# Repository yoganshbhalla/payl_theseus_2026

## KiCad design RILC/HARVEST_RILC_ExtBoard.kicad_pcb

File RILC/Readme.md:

Regolith Illumination for Light-based Characterisation
Extension Board for AS7331 and AS7343 Breakout Spectrometers, containing VIS, UV, NIR LEDs and control/driver circuitry.

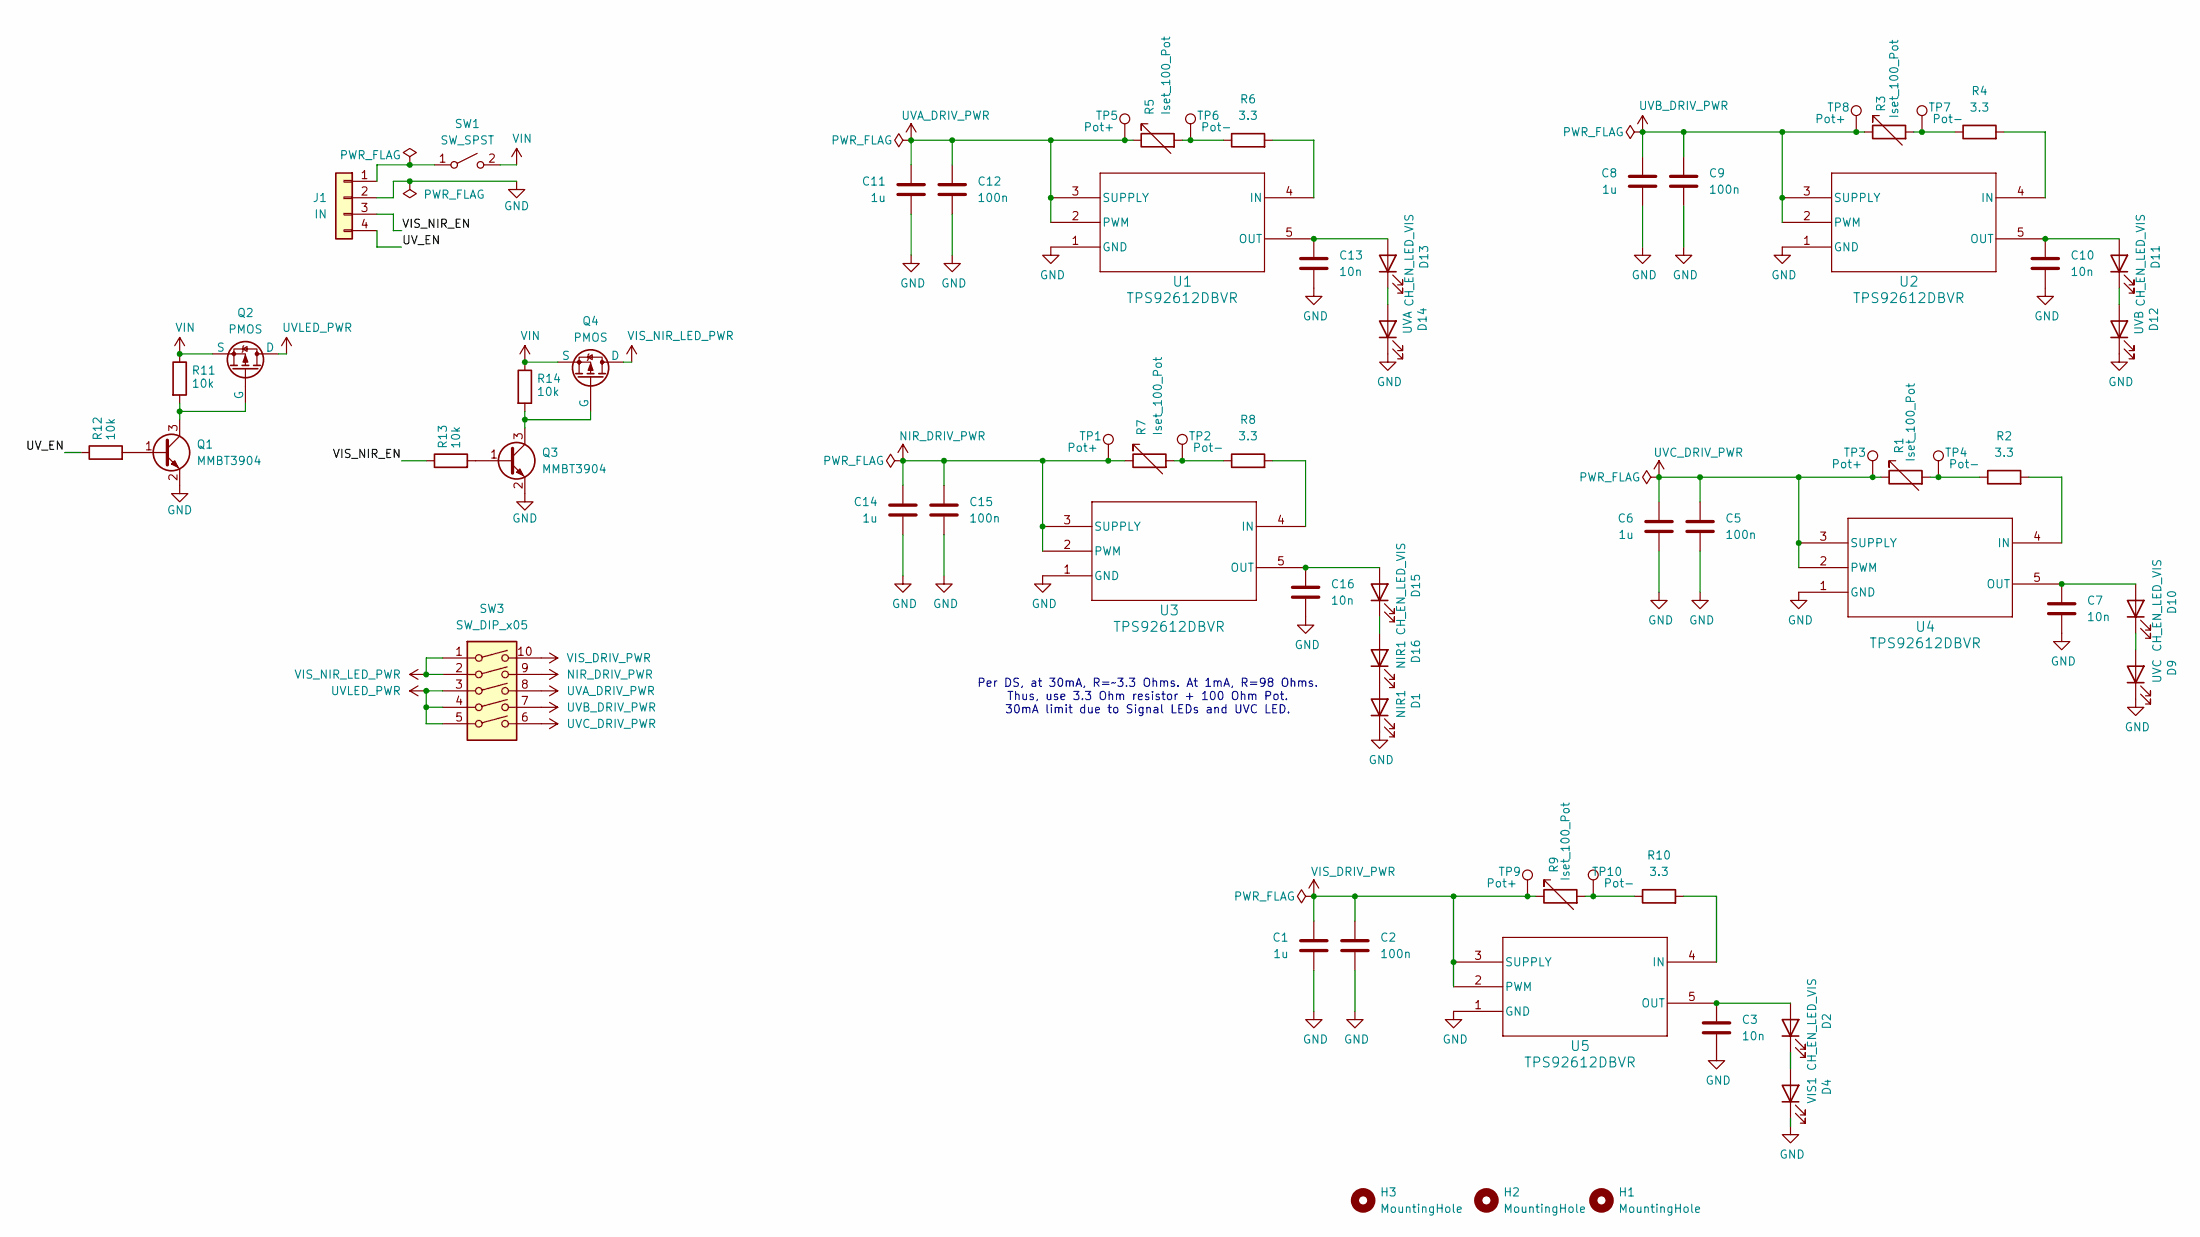
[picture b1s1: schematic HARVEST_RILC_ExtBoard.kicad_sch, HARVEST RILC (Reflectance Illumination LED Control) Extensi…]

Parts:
C1, C6, C8, C11, C14: 1u; C_0805_2012Metric_Pad1.18x1.45mm_HandSolder
C2, C5, C9, C12, C15: 100n; C_0805_2012Metric_Pad1.18x1.45mm_HandSolder
C3, C7, C10, C13, C16: 10n; C_0805_2012Metric_Pad1.18x1.45mm_HandSolder
D1, D16: NIR1; LED_0805_2012Metric_Pad1.15x1.40mm_HandSolder
D2, D10, D11, D13, D15: CH_EN_LED_VIS; LED_0805_2012Metric_Pad1.15x1.40mm_HandSolder
D4: VIS1; WL-SWTP_3014
D9: UVC; CR_0-275-120_VIS
D12: UVB; CHIP_1GF1A_SVI
D14: UVA; LED_0606
H1, H2, H3: MountingHole; MountingHole_2.2mm_M2
J1: IN; JST_XH_B4B-XH-A_1x04_P2.50mm_Vertical
Q1, Q3: MMBT3904; SOT-23
Q2, Q4: PMOS; SOT91P240X110-3N_DMG2305UX-7
R1, R3, R5, R7, R9: Iset_100_Pot; Potentiometer_Bourns_3296W_Vertical
R2, R4, R6, R8, R10: 3.3; R_0805_2012Metric_Pad1.20x1.40mm_HandSolder
R11, R12, R13, R14: 10k; R_0805_2012Metric_Pad1.20x1.40mm_HandSolder
SW1: SW_SPST; Switch_Toggle_SPDT_ANT11SF1CQE
SW3: SW_DIP_x05; SW_DIP_SPSTx05_Piano_CTS_Series194-5MSTN_W7.62mm_P2.54mm
TP1, TP3, TP5, TP8, TP9: Pot+; TestPoint_Pad_1.5x1.5mm
TP2, TP4, TP6, TP7, TP10: Pot-; TestPoint_Pad_1.5x1.5mm
U1, U2, U3, U4, U5: TPS92612DBVR; SOT_12DBVR_TEX

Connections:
/UV_EN: J1.4, R12.1
/VIS_NIR_EN: J1.3, R13.1
GND: C1.2, C2.2, C3.2, C5.2, C6.2, C7.2, C8.2, C9.2, C10.2, C11.2, C12.2, C13.2, C14.2, C15.2, C16.2, D1.1 (K), D4.1 (K), D9.1 (K), D12.1 (K), D14.1 (K), J1.2, Q1.2 (E), Q3.2 (E), U1.1 (GND), U2.1 (GND), U3.1 (GND), U4.1 (GND), U5.1 (GND)
NIR_DRIV_PWR: C14.1, C15.1, R7.1, SW3.9, TP1.1, U3.2 (PWM), U3.3 (SUPPLY)
unnamed: D1.2 (A), D16.1 (K)
unnamed: C3.1, D2.2 (A), U5.5 (OUT)
unnamed: D2.1 (K), D4.2 (A)
unnamed: C7.1, D10.2 (A), U4.5 (OUT)
unnamed: D9.2 (A), D10.1 (K)
unnamed: C10.1, D11.2 (A), U2.5 (OUT)
unnamed: D11.1 (K), D12.2 (A)
unnamed: C13.1, D13.2 (A), U1.5 (OUT)
unnamed: D13.1 (K), D14.2 (A)
unnamed: C16.1, D15.2 (A), U3.5 (OUT)
unnamed: D15.1 (K), D16.2 (A)
unnamed: J1.1, SW1.1 (A)
unnamed: Q1.1 (B), R12.2
unnamed: Q1.3 (C), Q2.2 (G), R11.2
unnamed: Q3.1 (B), R13.2
unnamed: Q3.3 (C), Q4.2 (G), R14.2
unnamed: R1.2, R2.1, TP4.1
unnamed: R3.2, R4.1, TP7.1
unnamed: R5.2, R6.1, TP6.1
unnamed: R7.2, R8.1, TP2.1
unnamed: R9.2, R10.1, TP10.1
unnamed: R6.2, U1.4 (IN)
unnamed: R4.2, U2.4 (IN)
unnamed: R8.2, U3.4 (IN)
unnamed: R2.2, U4.4 (IN)
unnamed: R10.2, U5.4 (IN)
UVA_DRIV_PWR: C11.1, C12.1, R5.1, SW3.8, TP5.1, U1.2 (PWM), U1.3 (SUPPLY)
UVB_DRIV_PWR: C8.1, C9.1, R3.1, SW3.7, TP8.1, U2.2 (PWM), U2.3 (SUPPLY)
UVC_DRIV_PWR: C5.1, C6.1, R1.1, SW3.6, TP3.1, U4.2 (PWM), U4.3 (SUPPLY)
UVLED_PWR: Q2.1 (D), SW3.3, SW3.4, SW3.5
VIN: Q2.3 (S), Q4.3 (S), R11.1, R14.1, SW1.2 (B)
VIS_DRIV_PWR: C1.1, C2.1, R9.1, SW3.10, TP9.1, U5.2 (PWM), U5.3 (SUPPLY)
VIS_NIR_LED_PWR: Q4.1 (D), SW3.1, SW3.2

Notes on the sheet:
Per DS, at 30mA, R=~3.3 Ohms. At 1mA, R=98 Ohms. Thus, use 3.3 Ohm resistor + 100 Ohm Pot. 30mA limit due to Signal LEDs and UVC LED.

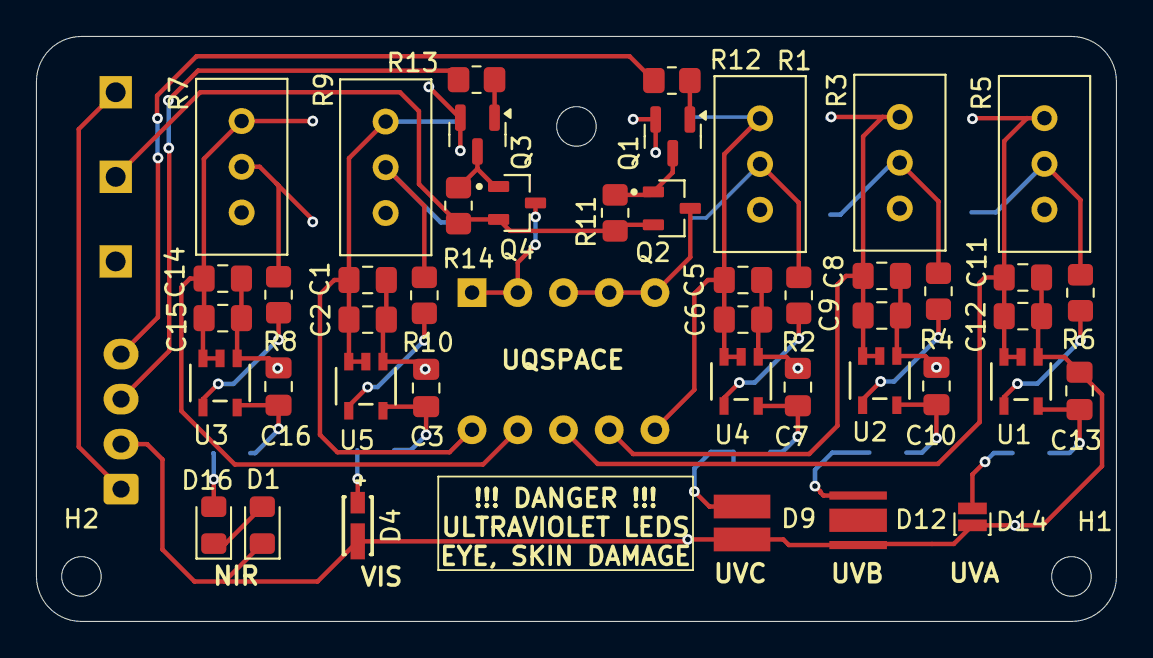
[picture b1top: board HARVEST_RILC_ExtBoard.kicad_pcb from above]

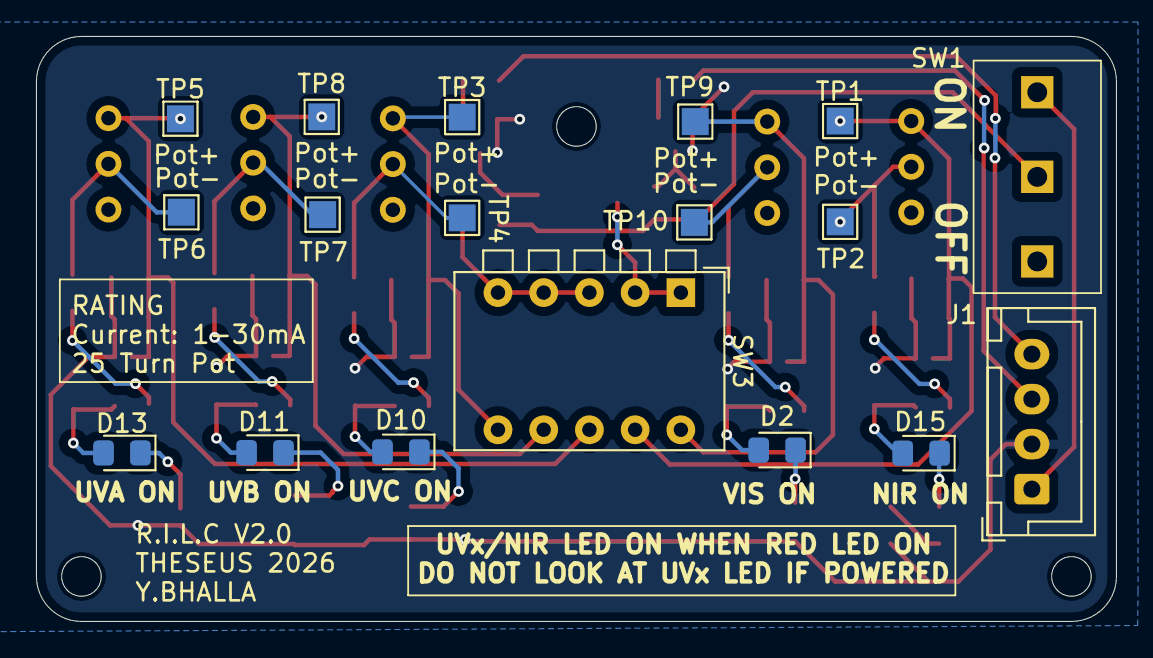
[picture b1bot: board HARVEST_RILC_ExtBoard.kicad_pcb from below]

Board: 2 copper layers, 60.0 x 32.5 mm, 65 parts (18 on the bottom side), 37 nets.

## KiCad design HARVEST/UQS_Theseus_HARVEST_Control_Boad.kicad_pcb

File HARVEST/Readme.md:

HARVEST PCB - See https://www.notion.so/uqspace/P-RV2601-HARVEST-301f47d1887680268325e2c343eff568

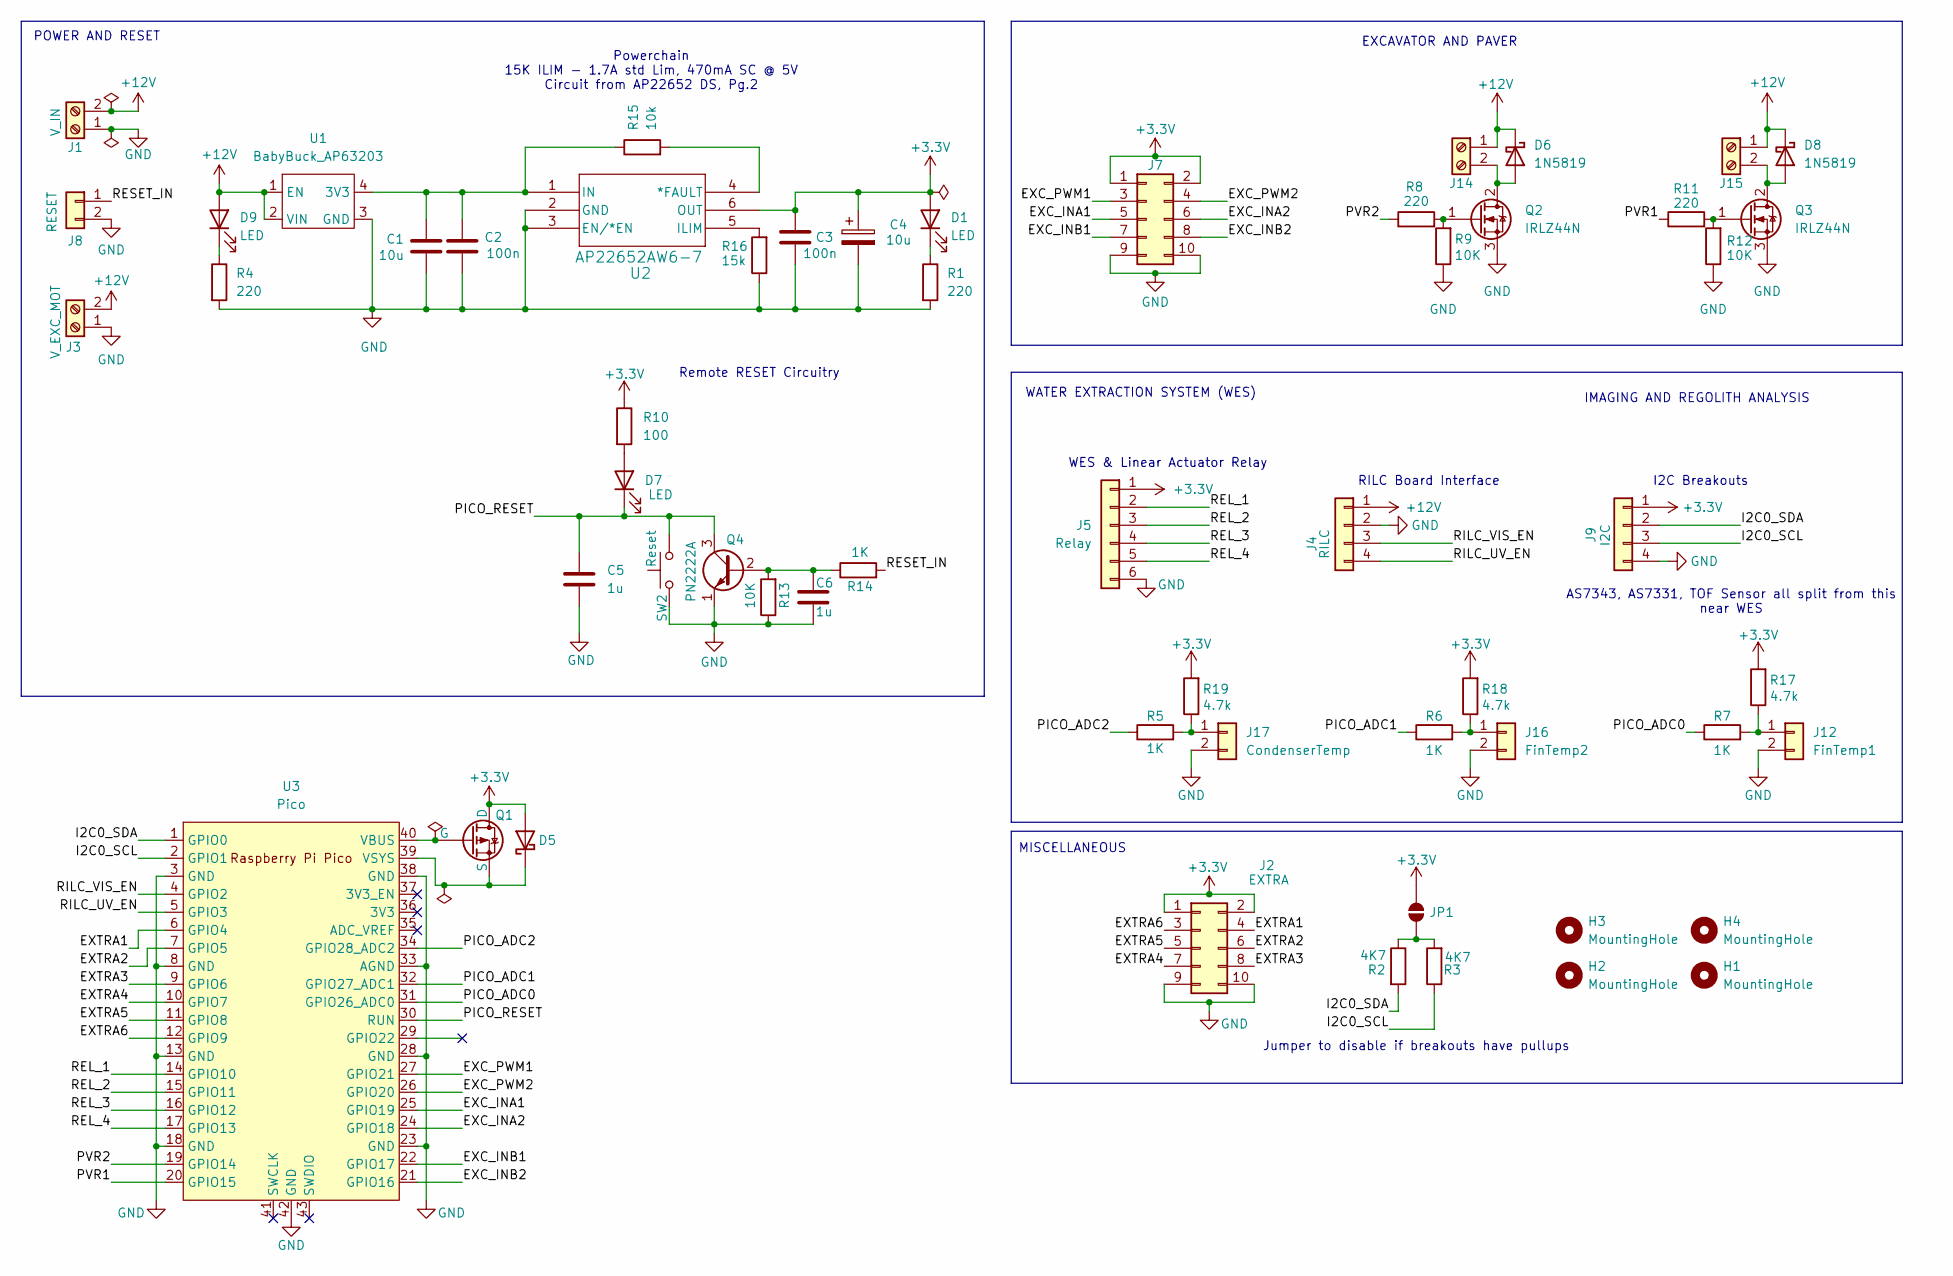
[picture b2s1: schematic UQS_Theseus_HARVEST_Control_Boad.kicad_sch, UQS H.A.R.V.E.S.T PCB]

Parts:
C1: 10u; C_0805_2012Metric_Pad1.18x1.45mm_HandSolder
C2, C3: 100n; C_0805_2012Metric_Pad1.18x1.45mm_HandSolder
C4: 10u; CP_Radial_D6.3mm_P2.50mm
C5, C6: 1u; C_0805_2012Metric_Pad1.18x1.45mm_HandSolder
D1, D7, D9: LED; LED_0805_2012Metric_Pad1.15x1.40mm_HandSolder
D5: D_Schottky; D_0805_2012Metric_Pad1.15x1.40mm_HandSolder
D6, D8: 1N5819; D_DO-41_SOD81_P10.16mm_Horizontal
H1, H2, H3, H4: MountingHole; MountingHole_3.2mm_M3
J1: V_IN; AMASS_XT30U-M_1x02_P5.0mm_Vertical
J2: EXTRA; PinHeader_2x05_P2.54mm_Vertical
J3: V_EXC_MOT; AMASS_XT30U-M_1x02_P5.0mm_Vertical
J4: RILC; JST_XH_B4B-XH-A_1x04_P2.50mm_Vertical
J5: Relay; JST_XH_B6B-XH-A_1x06_P2.50mm_Vertical
J7: MotorDriverSig; PinHeader_2x05_P2.54mm_Vertical
J8: RESET; PinHeader_1x02_P2.54mm_Vertical
J9: I2C; JST_XH_B4B-XH-A_1x04_P2.50mm_Vertical
J12: FinTemp1; JST_XH_B2B-XH-A_1x02_P2.50mm_Vertical
J14, J15: Screw_Terminal_01x02; TerminalBlock_RND_205-00012_1x02_P5.00mm_Horizontal
J16: FinTemp2; JST_XH_B2B-XH-A_1x02_P2.50mm_Vertical
J17: CondenserTemp; JST_XH_B2B-XH-A_1x02_P2.50mm_Vertical
JP1: SolderJumper_2_Open; SolderJumper-2_P1.3mm_Open_RoundedPad1.0x1.5mm
Q1: PMOS; SOT91P240X110-3N_DMG2305UX-7
Q2, Q3: IRLZ44N; TO-220-3_Vertical
Q4: PN2222A; TO-92_Inline
R1, R4, R8, R11: 220; R_0805_2012Metric_Pad1.20x1.40mm_HandSolder
R2, R3: 4K7; R_0805_2012Metric_Pad1.20x1.40mm_HandSolder
R5, R6, R7, R14: 1K; R_0805_2012Metric_Pad1.20x1.40mm_HandSolder
R9, R12, R13: 10K; R_0805_2012Metric_Pad1.20x1.40mm_HandSolder
R10: 100; R_0805_2012Metric_Pad1.20x1.40mm_HandSolder
R15: 10k; R_0805_2012Metric_Pad1.20x1.40mm_HandSolder
R16: 15k; R_0805_2012Metric_Pad1.20x1.40mm_HandSolder
R17, R18, R19: 4.7k; R_0805_2012Metric_Pad1.20x1.40mm_HandSolder
SW2: Reset; SW_PUSH_6mm_H4.3mm
U1: BabyBuck_AP63203; PinHeader_1x04_P2.54mm_Vertical
U2: AP22652AW6-7; AP22652A-M
U3: Pico; RPi_Pico_SMD_TH

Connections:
+3.3V: C3.1, C4.1, D1.2 (A), D5.2 (A), J2.1, J2.2, J5.1, J7.1, J7.2, J9.1, JP1.2 (B), Q1.1 (D), R10.1, R17.2, R18.2, R19.2, U2.6 (OUT)
+12V: D6.1 (K), D8.1 (K), D9.2 (A), J1.2, J3.2, J4.1, J14.1, J15.1, U1.1 (EN), U1.2 (VIN)
/EXC_INA1: J7.5, U3.25 (GPIO19)
/EXC_INA2: J7.6, U3.24 (GPIO18)
/EXC_INB1: J7.7, U3.22 (GPIO17)
/EXC_INB2: J7.8, U3.21 (GPIO16)
/EXC_PWM1: J7.3, U3.27 (GPIO21)
/EXC_PWM2: J7.4, U3.26 (GPIO20)
/EXTRA1: J2.4, U3.6 (GPIO4)
/EXTRA2: J2.6, U3.7 (GPIO5)
/EXTRA3: J2.8, U3.9 (GPIO6)
/EXTRA4: J2.7, U3.10 (GPIO7)
/EXTRA5: J2.5, U3.11 (GPIO8)
/EXTRA6: J2.3, U3.12 (GPIO9)
/I2C0_SCL: J9.3, R3.1, U3.2 (GPIO1)
/I2C0_SDA: J9.2, R2.2, U3.1 (GPIO0)
/PICO_ADC0: R7.1, U3.31 (GPIO26_ADC0)
/PICO_ADC1: R6.1, U3.32 (GPIO27_ADC1)
/PICO_ADC2: R5.1, U3.34 (GPIO28_ADC2)
/PICO_RESET: C5.1, D7.1 (K), Q4.3 (C), SW2.2, U3.30 (RUN)
/PVR1: R11.1, U3.20 (GPIO15)
/PVR2: R8.1, U3.19 (GPIO14)
/REL_1: J5.2, U3.14 (GPIO10)
/REL_2: J5.3, U3.15 (GPIO11)
/REL_3: J5.4, U3.16 (GPIO12)
/REL_4: J5.5, U3.17 (GPIO13)
/RESET_IN: J8.1, R14.2
/RILC_UV_EN: J4.4, U3.5 (GPIO3)
/RILC_VIS_EN: J4.3, U3.4 (GPIO2)
GND: C1.2, C2.2, C3.2, C4.2, C5.2, C6.2, J1.1, J2.9, J2.10, J3.1, J4.2, J5.6, J7.9, J7.10, J8.2, J9.4, J12.2, J16.2, J17.2, Q2.3 (S), Q3.3 (S), Q4.1 (E), R1.2, R4.2, R9.1, R12.1, R13.1, R16.1, SW2.1, U1.3 (GND), U2.2 (GND), U2.3 (EN/*EN), U3.3 (GND), U3.8 (GND), U3.13 (GND), U3.18 (GND), U3.23 (GND), U3.28 (GND), U3.33 (AGND), U3.38 (GND), U3.42 (GND)
unnamed: D1.1 (K), R1.1
unnamed: D5.1 (K), Q1.3 (S), U3.39 (VSYS)
unnamed: D6.2 (A), J14.2, Q2.2 (D)
unnamed: D7.2 (A), R10.2
unnamed: D8.2 (A), J15.2, Q3.2 (D)
unnamed: D9.1 (K), R4.1
unnamed: J12.1, R7.2, R17.1
unnamed: J16.1, R6.2, R18.1
unnamed: J17.1, R5.2, R19.1
unnamed: JP1.1 (A), R2.1, R3.2
unnamed: Q1.2 (G), U3.40 (VBUS)
unnamed: Q2.1 (G), R8.2, R9.2
unnamed: Q3.1 (G), R11.2, R12.2
unnamed: C6.1, Q4.2 (B), R13.2, R14.1
unnamed: C1.1, C2.1, R15.1, U1.4 (3V3), U2.1 (IN)
unnamed: R15.2, U2.4 (*FAULT)
unnamed: R16.2, U2.5 (ILIM)

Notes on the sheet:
I2C Breakouts
Jumper to disable if breakouts have pullups
RILC Board Interface
POWER AND RESET
MISCELLANEOUS
Powerchain 15K ILIM - 1.7A std Lim, 470mA SC @ 5V Circuit from AP22652 DS, Pg.2
Remote RESET Circuitry
EXCAVATOR AND PAVER
AS7343, AS7331, TOF Sensor all split from this near WES
WATER EXTRACTION SYSTEM (WES)
IMAGING AND REGOLITH ANALYSIS
WES & Linear Actuator Relay

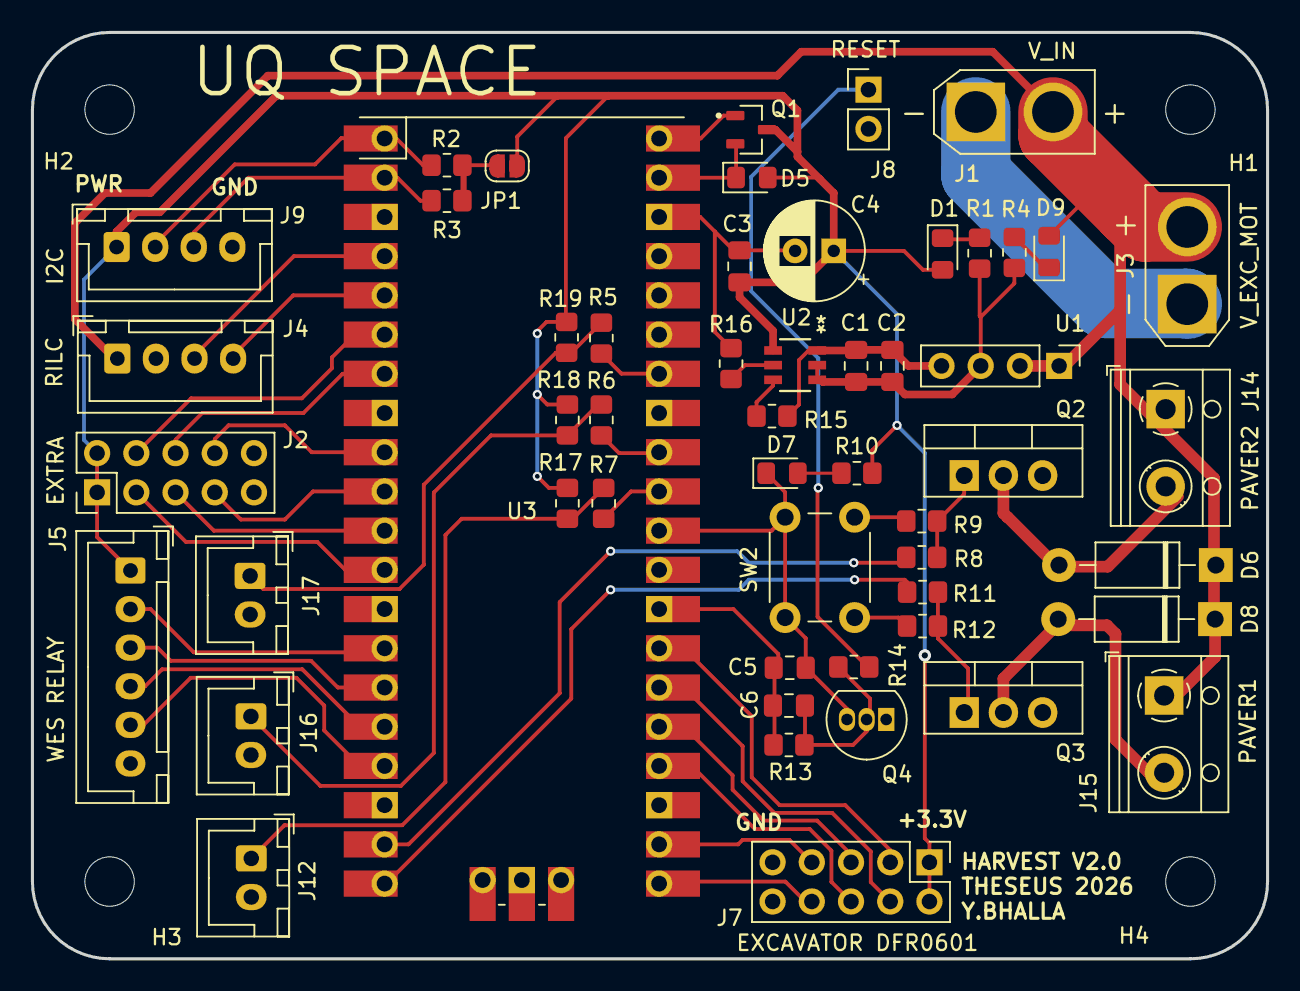
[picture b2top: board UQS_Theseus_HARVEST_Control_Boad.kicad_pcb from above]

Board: 2 copper layers, 80.0 x 60.0 mm, 57 parts (0 on the bottom side), 47 nets.

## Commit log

2026-02-09 V1.1
    UV, NIR LEDS. Ready for Prod.
2026-03-03 V2.0: Added eFuse
    HARVEST V2; Added eFuse for SC, OCP, Reverse Prot. Finished Silkscreen and fixed all valid warnings/errors. Production variant if review passed.
2026-03-03 V2.0: Produced Version
